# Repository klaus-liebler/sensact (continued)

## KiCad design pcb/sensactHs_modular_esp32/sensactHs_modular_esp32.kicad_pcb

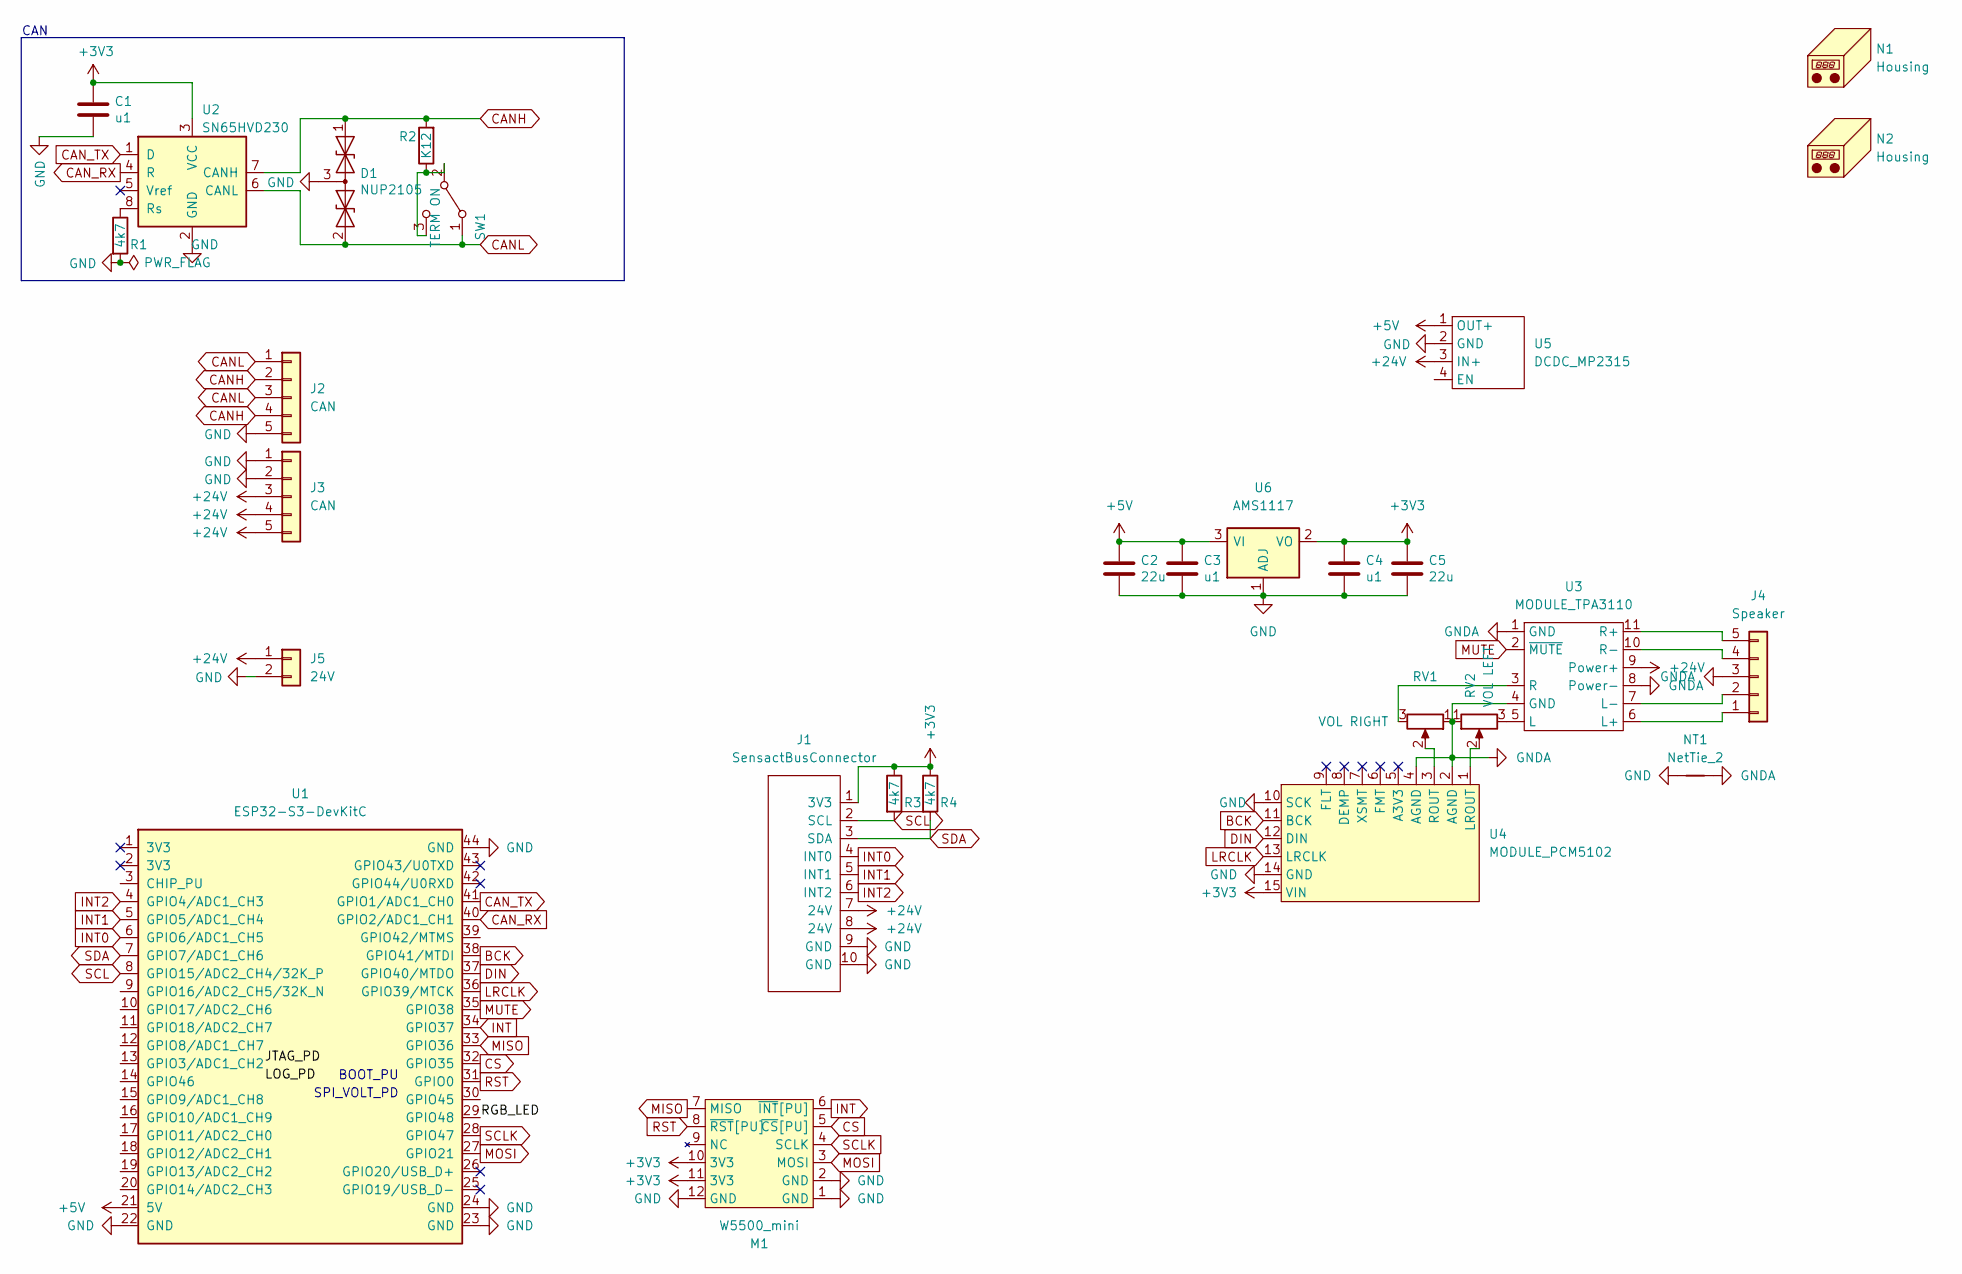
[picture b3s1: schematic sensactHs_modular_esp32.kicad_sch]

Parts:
C1, C3, C4: u1; C_0805_2012Metric_Pad1.18x1.45mm_HandSolder
C2, C5: 22u; C_1206_3216Metric_Pad1.33x1.80mm_HandSolder
D1: NUP2105; SOT-23_Handsoldering
J1: SensactBusConnector; IDC-Header_2x05_P2.54mm_Horizontal
J2, J3: CAN; PhoenixContact_MC_1,5_5-G-3.81_1x05_P3.81mm_Horizontal
J4: Speaker; PhoenixContact_MC_1,5_5-G-3.81_1x05_P3.81mm_Horizontal
J5: 24V; PhoenixContact_MC_1,5_2-G-3.5_1x02_P3.50mm_Horizontal
M1: W5500_mini; W5500-mini
N1, N2: Housing; KiCad-Logo2_5mm_SilkScreen
NT1: NetTie_2; NetTie-2_SMD_Pad2.0mm
R1, R3, R4: 4k7; R_0805_2012Metric_Pad1.20x1.40mm_HandSolder
R2: K12; R_1206_3216Metric_Pad1.30x1.75mm_HandSolder
RV1: VOL RIGHT; Potentiometer_Alps_RK09K_Single_Vertical
RV2: VOL LEFT; Potentiometer_Alps_RK09K_Single_Vertical
SW1: TERM ON; Switch_SS12D00
U1: ESP32-S3-DevKitC; AIthinker_ESP32_S3
U2: SN65HVD230; SOIC-8_3.9x4.9mm_P1.27mm
U3: MODULE_TPA3110; TPA3110_module
U4: MODULE_PCM5102; MODULE_PCM5102A
U5: DCDC_MP2315; MODULE_STEPDOWN
U6: AMS1117; SOT-223-3_TabPin2_HANDSOLDER

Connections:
+3V3: C1.1, C4.1, C5.1, J1.1 (3V3), M1.10 (3V3), M1.11 (3V3), R3.1, R4.1, U2.3 (VCC), U4.15 (VIN), U6.2 (VO)
+5V: C2.1, C3.1, U1.21 (5V), U5.1 (OUT+), U6.3 (VI)
+24V: J1.7 (24V), J1.8 (24V), J3.3, J3.4, J3.5, J5.1, U3.9 (Power+), U5.3 (IN+)
/RGB_LED: U1.29 (GPIO48)
BCK: U1.38 (GPIO41/MTDI), U4.11 (BCK)
CANH: D1.1 (A1), J2.2, J2.4, R2.2, U2.7 (CANH)
CANL: D1.2 (A2), J2.1, J2.3, SW1.1 (A), U2.6 (CANL)
CAN_RX: U1.40 (GPIO2/ADC1_CH1), U2.4 (R)
CAN_TX: U1.41 (GPIO1/ADC1_CH0), U2.1 (D)
CS: M1.5 (~CS[PU]), U1.32 (GPIO35)
DIN: U1.37 (GPIO40/MTDO), U4.12 (DIN)
GND: C1.2, C2.2, C3.2, C4.2, C5.2, D1.3 (common), J1.9 (GND), J1.10 (GND), J2.5, J3.1, J3.2, J5.2, M1.1 (GND), M1.2 (GND), M1.12 (GND), NT1.1, R1.2, U1.22 (GND), U1.23 (GND), U1.24 (GND), U1.44 (GND), U2.2 (GND), U4.10 (SCK), U4.14 (GND), U5.2 (GND), U6.1 (ADJ)
GNDA: J4.3, NT1.2, RV1.1, RV2.1, U3.1 (GND), U3.4 (GND), U3.8 (Power-), U4.2 (AGND), U4.4 (AGND)
INT: M1.6 (~INT[PU]), U1.34 (GPIO37)
INT0: J1.4 (INT0), U1.6 (GPIO6/ADC1_CH5)
INT1: J1.5 (INT1), U1.5 (GPIO5/ADC1_CH4)
INT2: J1.6 (INT2), U1.4 (GPIO4/ADC1_CH3)
LRCLK: U1.36 (GPIO39/MTCK), U4.13 (LRCLK)
MISO: M1.7 (MISO), U1.33 (GPIO36)
MOSI: M1.3 (MOSI), U1.27 (GPIO21)
MUTE: U1.35 (GPIO38), U3.2 (~MUTE)
unnamed: J4.1, U3.6 (L+)
unnamed: J4.2, U3.7 (L-)
unnamed: J4.4, U3.10 (R-)
unnamed: J4.5, U3.11 (R+)
unnamed: R1.1, U2.8 (Rs)
unnamed: R2.1, SW1.2 (B), SW1.3 (C)
unnamed: RV1.2, U4.3 (ROUT)
unnamed: RV1.3, U3.3 (R)
unnamed: RV2.2, U4.1 (LROUT)
unnamed: RV2.3, U3.5 (L)
RST: M1.8 (~RST[PU]), U1.31 (GPIO0)
SCL: J1.2 (SCL), R3.2, U1.8 (GPIO15/ADC2_CH4/32K_P)
SCLK: M1.4 (SCLK), U1.28 (GPIO47)
SDA: J1.3 (SDA), R4.2, U1.7 (GPIO7/ADC1_CH6)

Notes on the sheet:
CAN
BOOT_PU
SPI_VOLT_PD

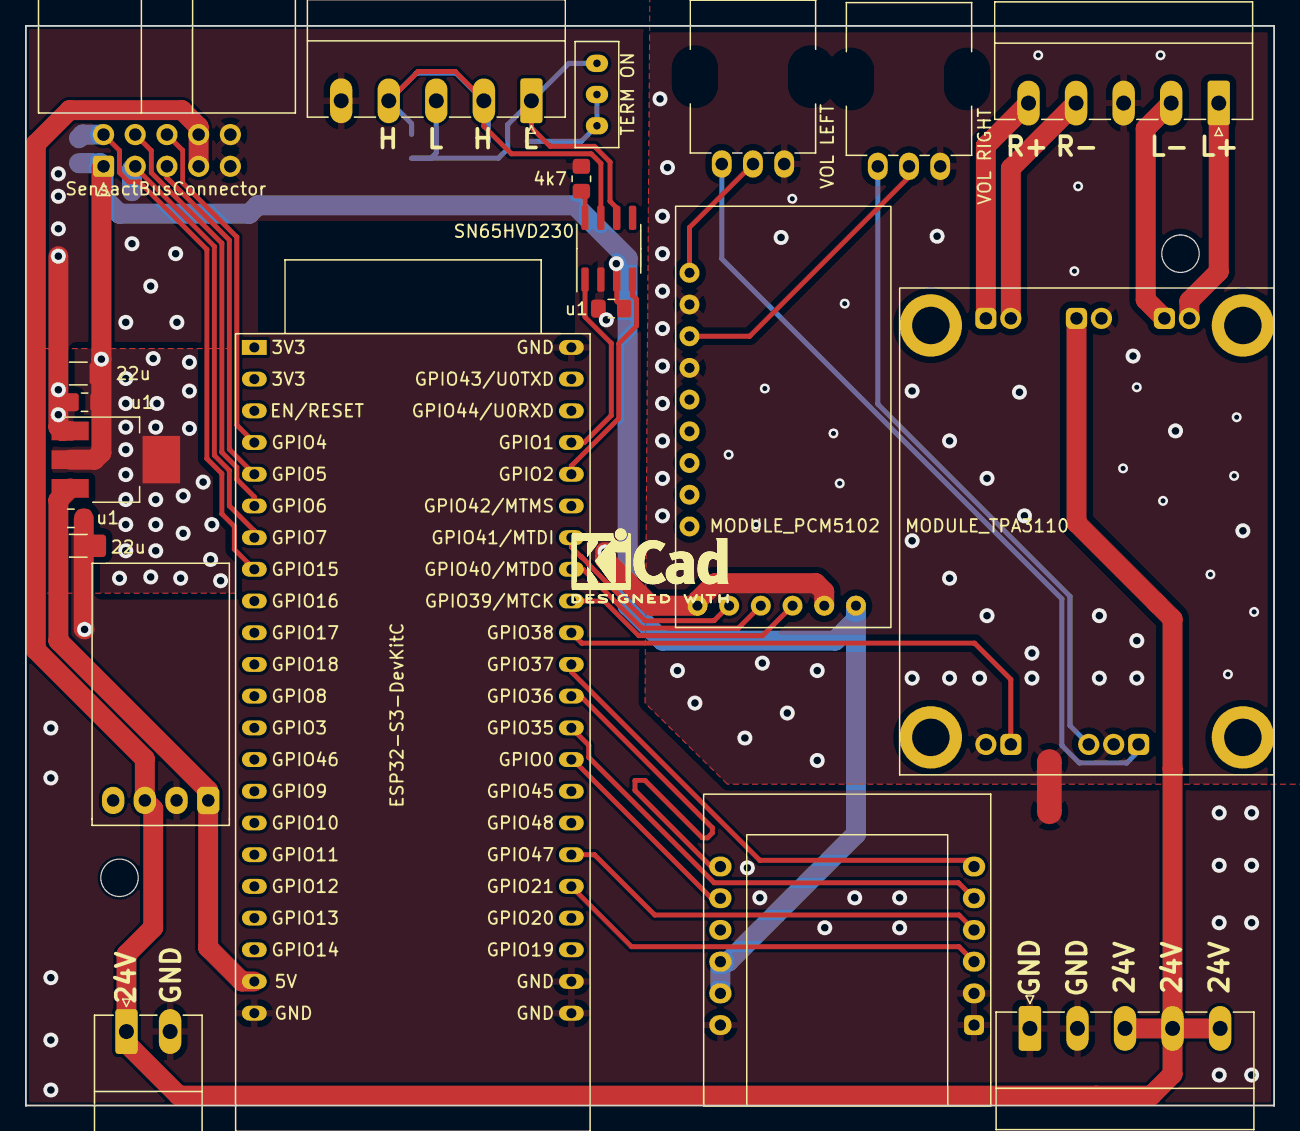
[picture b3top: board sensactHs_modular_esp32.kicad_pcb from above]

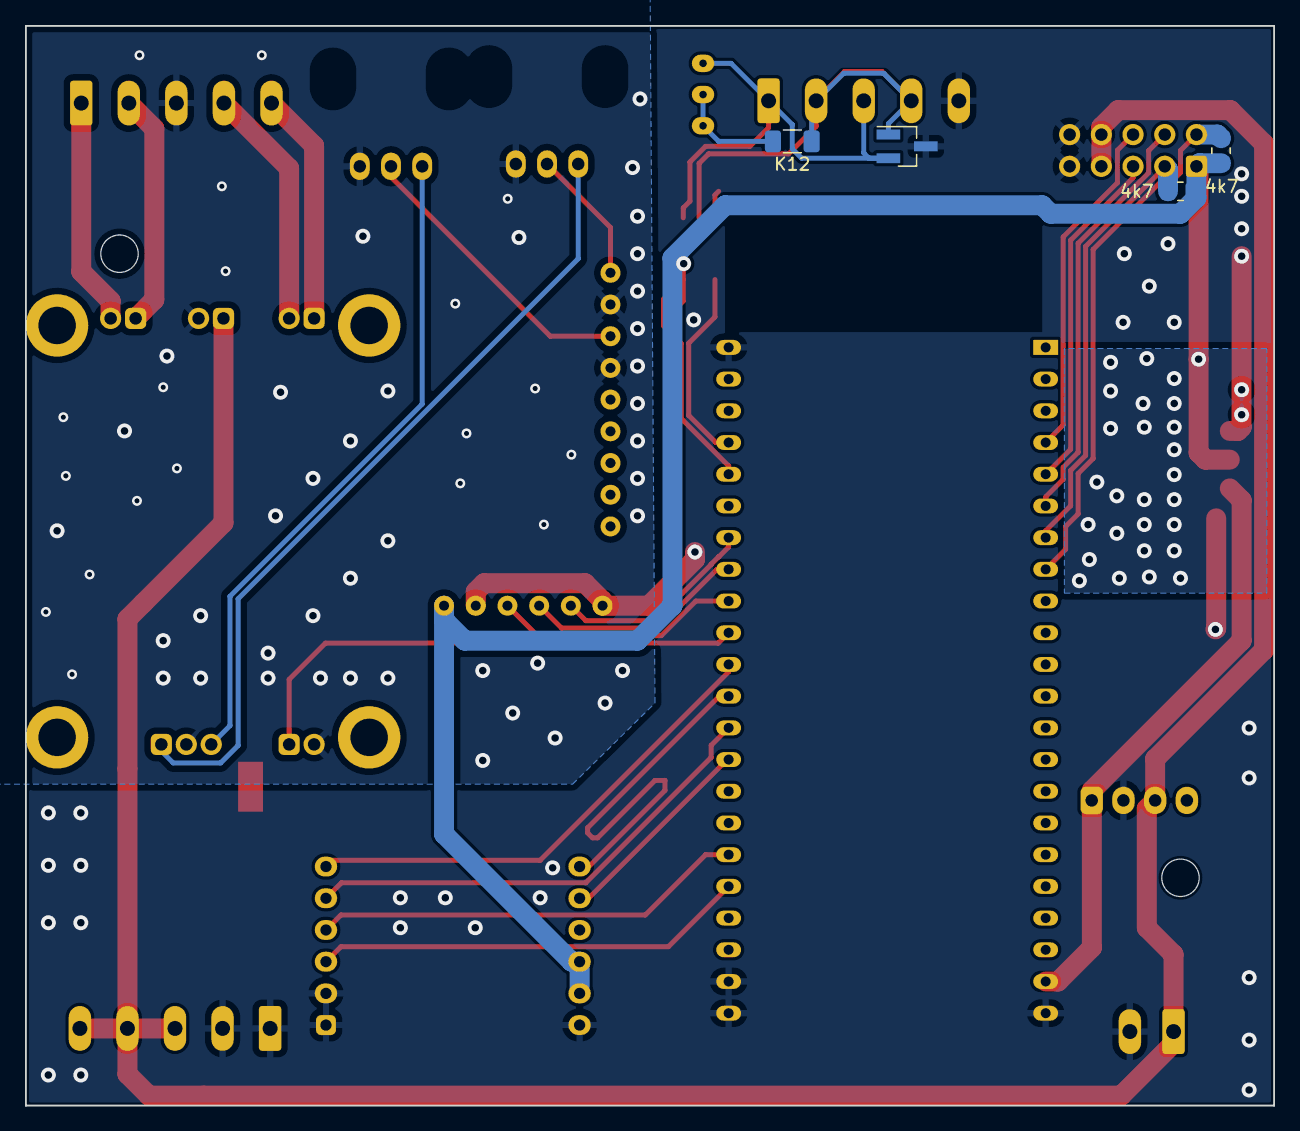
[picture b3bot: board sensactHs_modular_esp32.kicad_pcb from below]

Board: 2 copper layers, 100.0 x 86.5 mm, 28 parts (4 on the bottom side), 34 nets.

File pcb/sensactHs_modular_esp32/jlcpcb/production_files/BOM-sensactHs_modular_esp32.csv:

Comment,Designator,Footprint,LCSC
VOL LEFT,RV2,Potentiometer_Alps_RK09K_Single_Vertical,
Housing,N1,KiCad-Logo2_5mm_SilkScreen,
u1,C1,C_0805_2012Metric_Pad1.18x1.45mm_HandSolder,
AMS1117,U6,SOT-223-3_TabPin2_HANDSOLDER,
CAN,J2,"PhoenixContact_MC_1,5_5-G-3.81_1x05_P3.81mm_Horizontal",
24V,J5,"PhoenixContact_MC_1,5_2-G-3.5_1x02_P3.50mm_Horizontal",
NetTie_2,NT1,NetTie-2_SMD_Pad2.0mm,
DCDC_MP2315,U5,MODULE_STEPDOWN,
MODULE_TPA3110,U3,TPA3110_module,
Housing,N2,KiCad-Logo2_5mm_SilkScreen,
CAN,J3,"PhoenixContact_MC_1,5_5-G-3.81_1x05_P3.81mm_Horizontal",
Speaker,J4,"PhoenixContact_MC_1,5_5-G-3.81_1x05_P3.81mm_Horizontal",
SN65HVD230,U2,SOIC-8_3.9x4.9mm_P1.27mm,
22u,C5,C_1206_3216Metric_Pad1.33x1.80mm_HandSolder,
MODULE_PCM5102,U4,MODULE_PCM5102A,
TERM ON,SW1,Switch_SS12D00,
ESP32-S3-DevKitC,U1,AIthinker_ESP32_S3,
W5500_mini,M1,W5500-mini,
VOL RIGHT,RV1,Potentiometer_Alps_RK09K_Single_Vertical,
u1,C3,C_0805_2012Metric_Pad1.18x1.45mm_HandSolder,
22u,C2,C_1206_3216Metric_Pad1.33x1.80mm_HandSolder,
u1,C4,C_0805_2012Metric_Pad1.18x1.45mm_HandSolder,
4k7,R1,R_0805_2012Metric_Pad1.20x1.40mm_HandSolder,
SensactBusConnector,J1,IDC-Header_2x05_P2.54mm_Horizontal,
NUP2105,D1,SOT-23_Handsoldering,
K12,R2,R_1206_3216Metric_Pad1.30x1.75mm_HandSolder,
4k7,R4,R_0805_2012Metric_Pad1.20x1.40mm_HandSolder,
4k7,R3,R_0805_2012Metric_Pad1.20x1.40mm_HandSolder,

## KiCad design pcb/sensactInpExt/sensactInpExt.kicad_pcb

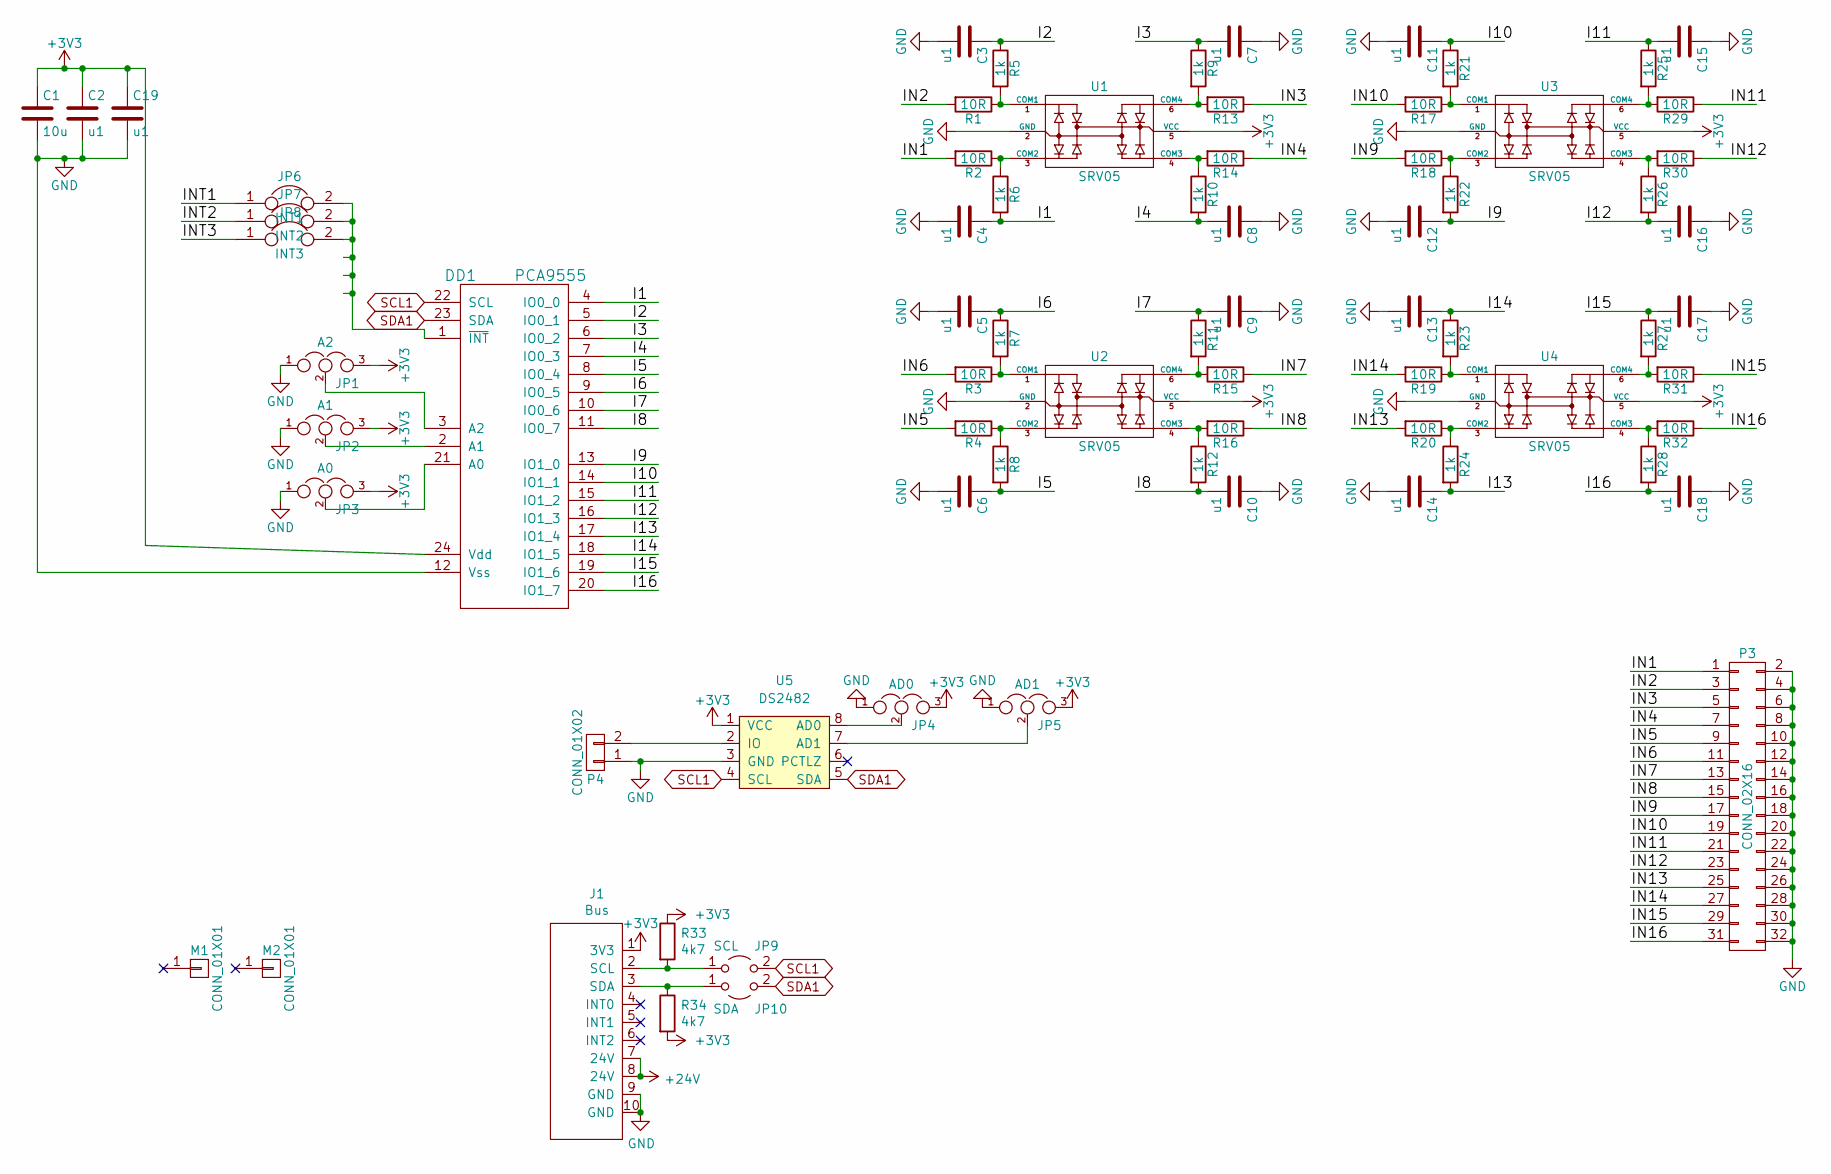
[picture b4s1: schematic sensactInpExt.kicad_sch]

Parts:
C1: 10u; C_1210_HandSoldering
C2, C3, C4, C5, C6, C7, C8, C9, C10, C11, C12, C13, C14, C15, C16, C17, C18, C19: u1; C_0805_HandSoldering
DD1: PCA9555; TSSOP-24_4.4x7.8mm_Pitch0.65mm_handsolder
J1: Bus; IDC-Header_2x05_P2.54mm_Horizontal_tightCrtYd
JP1: A2; SMD-solder-bridge-3pin
JP2: A1; SMD-solder-bridge-3pin
JP3: A0; SMD-solder-bridge-3pin
JP4: AD0; SMD-solder-bridge-3pin
JP5: AD1; SMD-solder-bridge-3pin
JP6: INT1; SMD-solder-bridge
JP7: INT2; SMD-solder-bridge
JP8: INT3; SMD-solder-bridge
JP9: SCL; SolderJumper-2_P1.3mm_Bridged2Bar_RoundedPad1.0x1.5mm
JP10: SDA; SolderJumper-2_P1.3mm_Bridged2Bar_RoundedPad1.0x1.5mm
M1, M2: CONN_01X01; MountingHole_4.3mm_M4_DIN965
P3: CONN_02X16; vasch_strip_16x2
P4: CONN_01X02; KF141R-2p
R1, R2, R3, R4, R13, R14, R15, R16, R17, R18, R19, R20, R29, R30, R31, R32: 10R; R_0805_HandSoldering
R5, R6, R7, R8, R9, R10, R11, R12, R21, R22, R23, R24, R25, R26, R27, R28: 1k; R_0805_HandSoldering
R33, R34: 4k7; R_0402_1005Metric
U1, U2, U3, U4: SRV05; SOT-23-6_handsolder
U5: DS2482; SOIC-8_3.9x4.9mm_P1.27mm

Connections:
+3V3: C1.1, C2.1, C19.1, DD1.24 (Vdd), J1.1 (3V3), JP1.3, JP2.3, JP3.3, JP4.3, JP5.3, R33.1, R34.2, U1.5 (VCC), U2.5 (VCC), U3.5 (VCC), U4.5 (VCC), U5.1 (VCC); also elsewhere on the board
/I1: C4.1, DD1.4 (IO0_0), R6.2
/I2: C3.1, DD1.5 (IO0_1), R5.1
/I3: C7.2, DD1.6 (IO0_2), R9.1
/I4: C8.2, DD1.7 (IO0_3), R10.2
/I5: C6.1, DD1.8 (IO0_4), R8.2
/I6: C5.1, DD1.9 (IO0_5), R7.1
/I7: C9.2, DD1.10 (IO0_6), R11.1
/I8: C10.2, DD1.11 (IO0_7), R12.2
/I9: C12.1, DD1.13 (IO1_0), R22.2
/I10: C11.1, DD1.14 (IO1_1), R21.1
/I11: C15.2, DD1.15 (IO1_2), R25.1
/I12: C16.2, DD1.16 (IO1_3), R26.2
/I13: C14.1, DD1.17 (IO1_4), R24.2
/I14: C13.1, DD1.18 (IO1_5), R23.1
/I15: C17.2, DD1.19 (IO1_6), R27.1
/I16: C18.2, DD1.20 (IO1_7), R28.2
/IN1: P3.1, R2.2
/IN2: P3.3, R1.2
/IN3: P3.5, R13.1
/IN4: P3.7, R14.1
/IN5: P3.9, R4.2
/IN6: P3.11, R3.2
/IN7: P3.13, R15.1
/IN8: P3.15, R16.1
/IN9: P3.17, R18.2
/IN10: P3.19, R17.2
/IN11: P3.21, R29.1
/IN12: P3.23, R30.1
/IN13: P3.25, R20.2
/IN14: P3.27, R19.2
/IN15: P3.29, R31.1
/IN16: P3.31, R32.1
/INT1: JP6.1; also elsewhere on the board
/INT2: JP7.1; also elsewhere on the board
/INT3: JP8.1; also elsewhere on the board
/SCL: DD1.22 (SCL), JP9.2 (B), U5.4 (SCL); also elsewhere on the board
/SDA: DD1.23 (SDA), JP10.2 (B), U5.5 (SDA); also elsewhere on the board
GND: C1.2, C2.2, C3.2, C4.2, C5.2, C6.2, C7.1, C8.1, C9.1, C10.1, C11.2, C12.2, C13.2, C14.2, C15.1, C16.1, C17.1, C18.1, C19.2, DD1.12 (Vss), J1.9 (GND), J1.10 (GND), JP1.1, JP2.1, JP3.1, JP4.1, JP5.1, P3.2, P3.4, P3.6, P3.8, P3.10, P3.12, P3.14, P3.16, P3.18, P3.20, P3.22, P3.24, P3.26, P3.28, P3.30, P3.32, P4.1, U1.2 (GND), U2.2 (GND), U3.2 (GND), U4.2 (GND), U5.3 (GND); also elsewhere on the board
unnamed: DD1.1 (~INT), JP6.2, JP7.2, JP8.2
unnamed: DD1.2 (A1), JP2.2
unnamed: DD1.3 (A2), JP1.2
unnamed: DD1.21 (A0), JP3.2
unnamed: J1.2 (SCL), JP9.1 (A), R33.2
unnamed: J1.3 (SDA), JP10.1 (A), R34.1
unnamed: J1.7 (24V), J1.8 (24V)
unnamed: JP4.2, U5.8 (AD0)
unnamed: JP5.2, U5.7 (AD1)
unnamed: P4.2, U5.2 (IO)
unnamed: R1.1, R5.2, U1.1 (COM1)
unnamed: R2.1, R6.1, U1.3 (COM2)
unnamed: R3.1, R7.2, U2.1 (COM1)
unnamed: R4.1, R8.1, U2.3 (COM2)
unnamed: R10.1, R14.2, U1.4 (COM3)
unnamed: R11.2, R15.2, U2.6 (COM4)
unnamed: R12.1, R16.2, U2.4 (COM3)
unnamed: R9.2, R13.2, U1.6 (COM4)
unnamed: R17.1, R21.2, U3.1 (COM1)
unnamed: R18.1, R22.1, U3.3 (COM2)
unnamed: R19.1, R23.2, U4.1 (COM1)
unnamed: R20.1, R24.1, U4.3 (COM2)
unnamed: R25.2, R29.2, U3.6 (COM4)
unnamed: R26.1, R30.2, U3.4 (COM3)
unnamed: R27.2, R31.2, U4.6 (COM4)
unnamed: R28.1, R32.2, U4.4 (COM3)

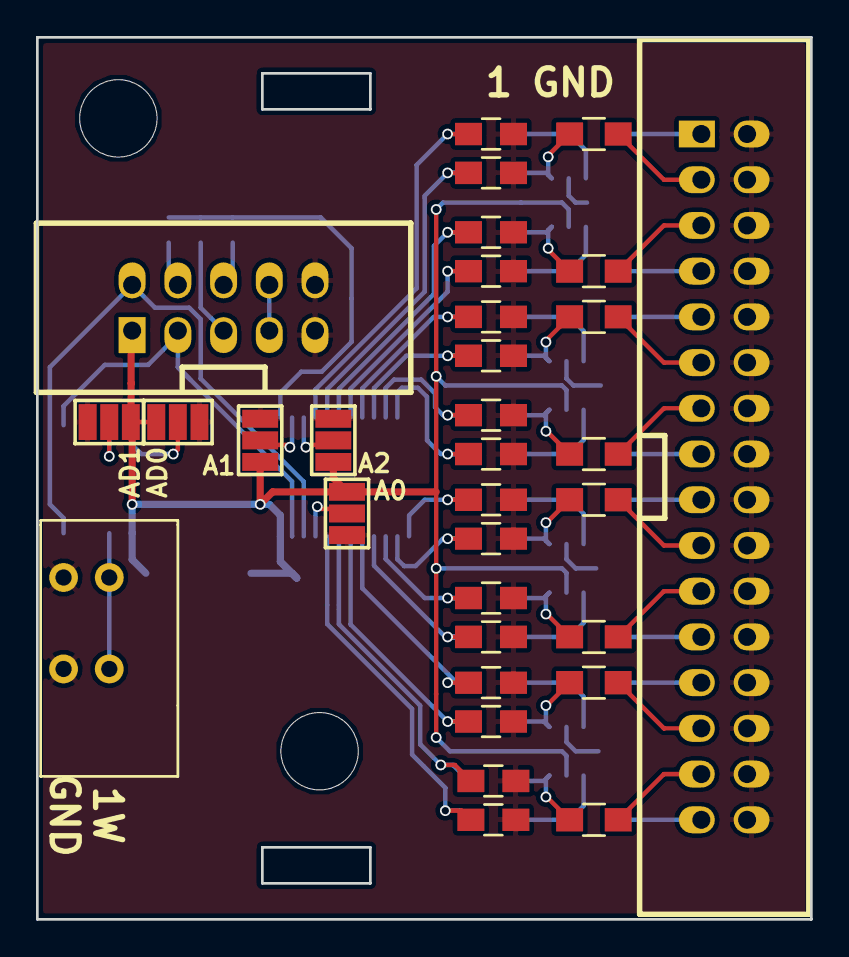
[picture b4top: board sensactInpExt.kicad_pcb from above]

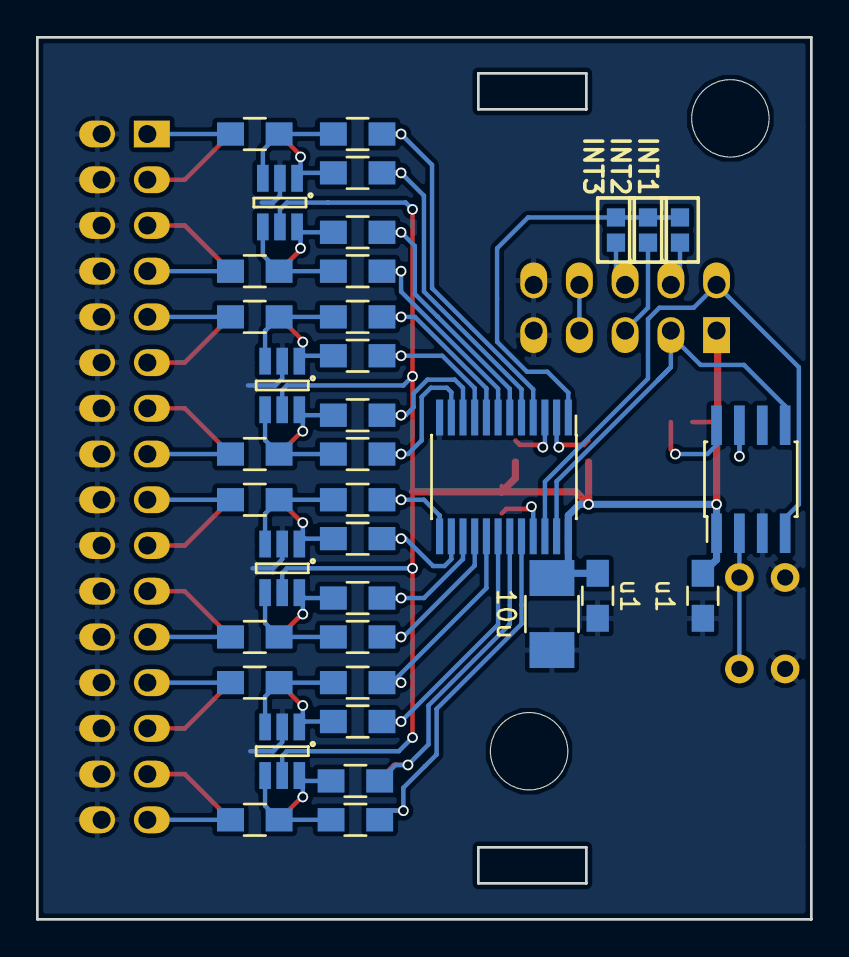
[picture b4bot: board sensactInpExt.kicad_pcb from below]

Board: 2 copper layers, 43.0 x 49.0 mm, 70 parts (36 on the bottom side), 63 nets.

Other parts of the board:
P2: CONN_02X05; vasch_strip_5x2

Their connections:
+3V3: P2.1; also elsewhere on the board
+24V: P2.7, P2.8
/INT1: P2.4; also elsewhere on the board
/INT2: P2.5; also elsewhere on the board
/INT3: P2.6; also elsewhere on the board
/SCL: P2.2; also elsewhere on the board
/SDA: P2.3; also elsewhere on the board
GND: P2.9, P2.10; also elsewhere on the board

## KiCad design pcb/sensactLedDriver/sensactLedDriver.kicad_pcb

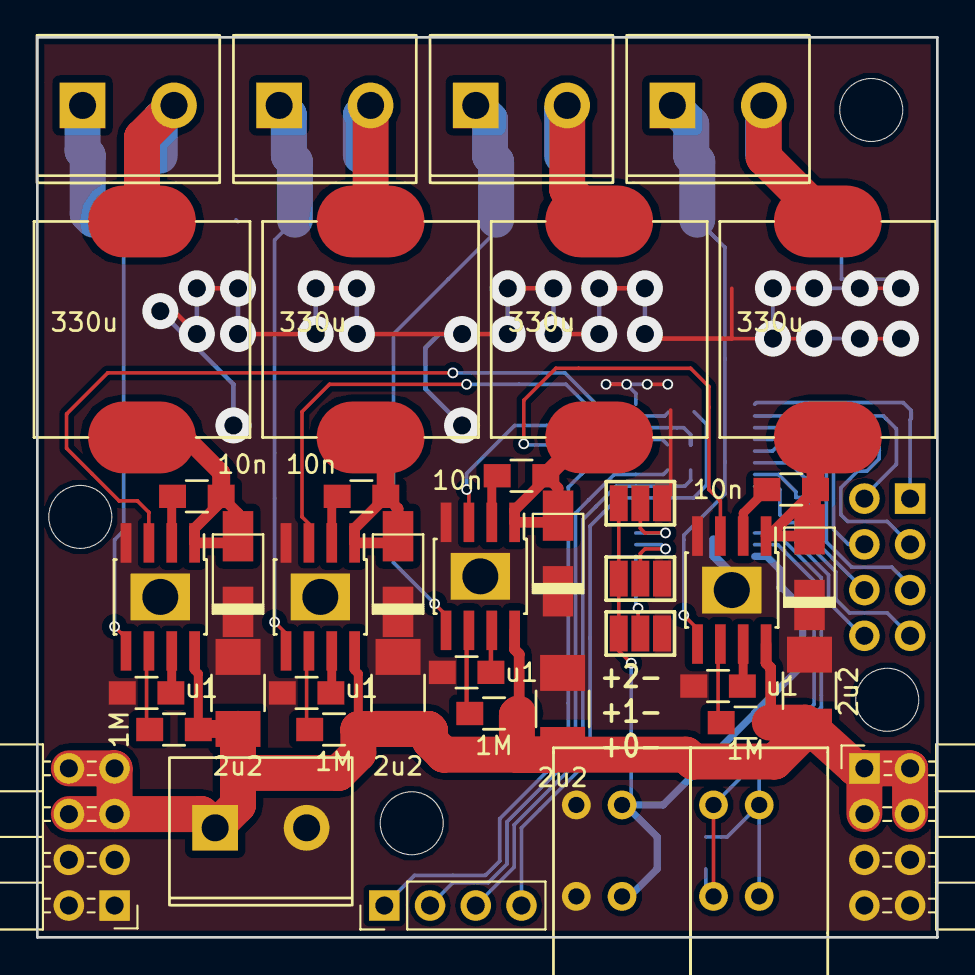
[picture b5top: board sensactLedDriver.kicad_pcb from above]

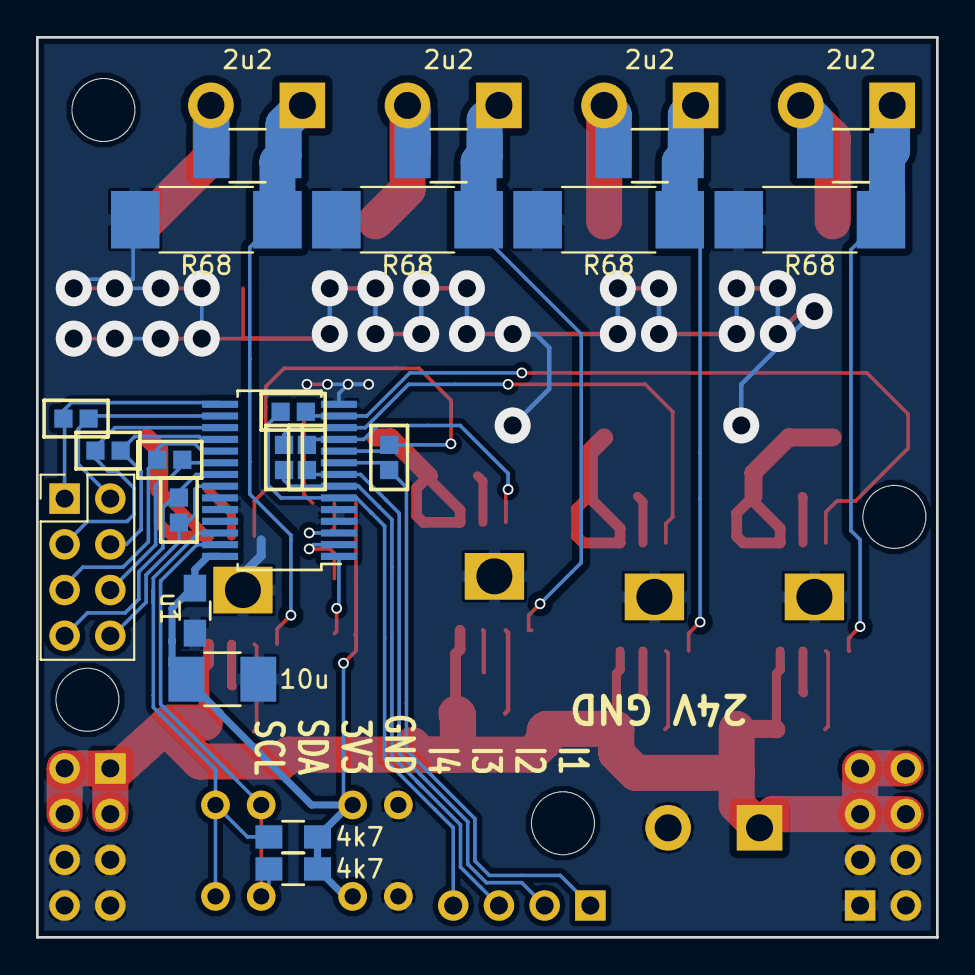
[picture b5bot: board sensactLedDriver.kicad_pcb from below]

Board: 2 copper layers, 50.0 x 50.0 mm, 67 parts (22 on the bottom side), 48 nets.

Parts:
C8: u1; C_0805_HandSoldering
C9: 10u; C_1210_HandSoldering
C10, C13, C14, C17, C18, C21, C22, C25: 2u2; R_1210_HandSoldering
C11, C15, C19, C23: 10n; R_0805_HandSoldering
C12, C16, C20, C24: u1; R_0805_HandSoldering
D1, D2, D3, D4: D_Schottky; do214ac_handsolder
JP1, JP2, JP6, JP7, JP8, JP9, JP10, JP11: Jumper_NO_Small; SMD-solder-bridge
JP3, JP4, JP5: JUMPER3; SMD-solder-bridge-3pin
L1, L2, L3, L4: 330u; CD127
P1, P5: CONN_01X02; KF141R-2p
P2, P7, P8, P9, P10: CONN_01X02; conn_2P
P3, P3#2, P3#3, P4: CONN_01X01; MountingHole_3.5mm
P6: CONN_01X04; Pin_Header_Straight_1x04_Pitch2.54mm
P11, P21: CONN_02X04; Pin_Header_Angled_2x04_Pitch2.54mm
P16: CONN_01X08; Pin_Header_Straight_2x04_Pitch2.54mm
R1, R2: 4k7; R_0805_HandSoldering
R3, R5, R7, R9: 1M; R_0805_HandSoldering
R4, R6, R8, R10: R68; R_2512_HandSoldering
U1: PCA9685; TSSOP-28_4.4x9.7mm_Pitch0.65mm_handsolder
U2, U3, U4, U5: LM3404; SOIC-8_3.9x4.9mm_Pitch1.27mm_pad_handsolder

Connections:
+3V3: C8.1, C9.1, JP3.1, JP4.1, JP5.1, P1.2, R1.1, R2.1, U1.28
+24V: C10.1, C14.1, C18.1, C22.1, P2.1, P11.1, P11.2, P11.3, P11.4, P21.5, P21.6, P21.7, P21.8, R3.1, R5.1, R7.1, R9.1, U2.8, U3.8, U4.8, U5.8
/A0: JP3.2, U1.1
/A1: JP4.2, U1.2
/A2: JP5.2, U1.3
/SCL: P5.2, R1.2, U1.26
/SDA: P5.1, R2.2, U1.27
/pwm1/LED+: C13.1, L1.1, P7.2
/pwm1/LED-: C13.2, P7.1, R4.1, U2.5
/pwm1/PWM_IN: JP6.2, U1.13, U2.3
/pwm2/LED+: C17.1, L2.1, P8.2
/pwm2/LED-: C17.2, P8.1, R6.1, U3.5
/pwm2/PWM_IN: JP7.2, U1.12, U3.3
/pwm3/LED+: C21.1, L3.1, P9.2
/pwm3/LED-: C21.2, P9.1, R8.1, U4.5
/pwm3/PWM_IN: JP8.2, U1.11, U4.3
/pwm4/LED+: C25.1, L4.1, P10.2
/pwm4/LED-: C25.2, P10.1, R10.1, U5.5
/pwm4/PWM_IN: JP9.2, U1.10, U5.3
GND: C8.2, C9.2, C10.2, C12.2, C14.2, C16.2, C18.2, C20.2, C22.2, C24.2, D1.2, D2.2, D3.2, D4.2, JP3.3, JP4.3, JP5.3, P1.1, P2.2, P11.5, P11.6, P11.7, P11.8, P21.1, P21.2, P21.3, P21.4, R4.2, R6.2, R8.2, R10.2, U1.4, U1.5, U1.14, U1.23, U1.24, U2.4, U2.9, U3.4, U3.9, U4.4, U4.9, U5.4, U5.9
unnamed: C11.1, D1.1, L1.2, U2.1
unnamed: C11.2, U2.2
unnamed: C12.1, U2.7
unnamed: C15.1, D2.1, L2.2, U3.1
unnamed: C15.2, U3.2
unnamed: C16.1, U3.7
unnamed: C19.1, D3.1, L3.2, U4.1
unnamed: C19.2, U4.2
unnamed: C20.1, U4.7
unnamed: C23.1, D4.1, L4.2, U5.1
unnamed: C23.2, U5.2
unnamed: C24.1, U5.7
unnamed: JP1.1, P16.8, U1.22
unnamed: JP1.2, P16.7, U1.21
unnamed: JP2.1, P16.4, U1.18
unnamed: JP2.2, P16.3, U1.17
unnamed: JP6.1, P6.4, U1.6
unnamed: JP7.1, P6.3, U1.7
unnamed: JP8.1, P6.2, U1.8
unnamed: JP9.1, P6.1, U1.9
unnamed: JP10.1, P16.6, U1.20
unnamed: JP10.2, P16.5, U1.19
unnamed: JP11.1, P16.2, U1.16
unnamed: JP11.2, P16.1, U1.15
unnamed: R3.2, U2.6
unnamed: R5.2, U3.6
unnamed: R7.2, U4.6
unnamed: R9.2, U5.6
